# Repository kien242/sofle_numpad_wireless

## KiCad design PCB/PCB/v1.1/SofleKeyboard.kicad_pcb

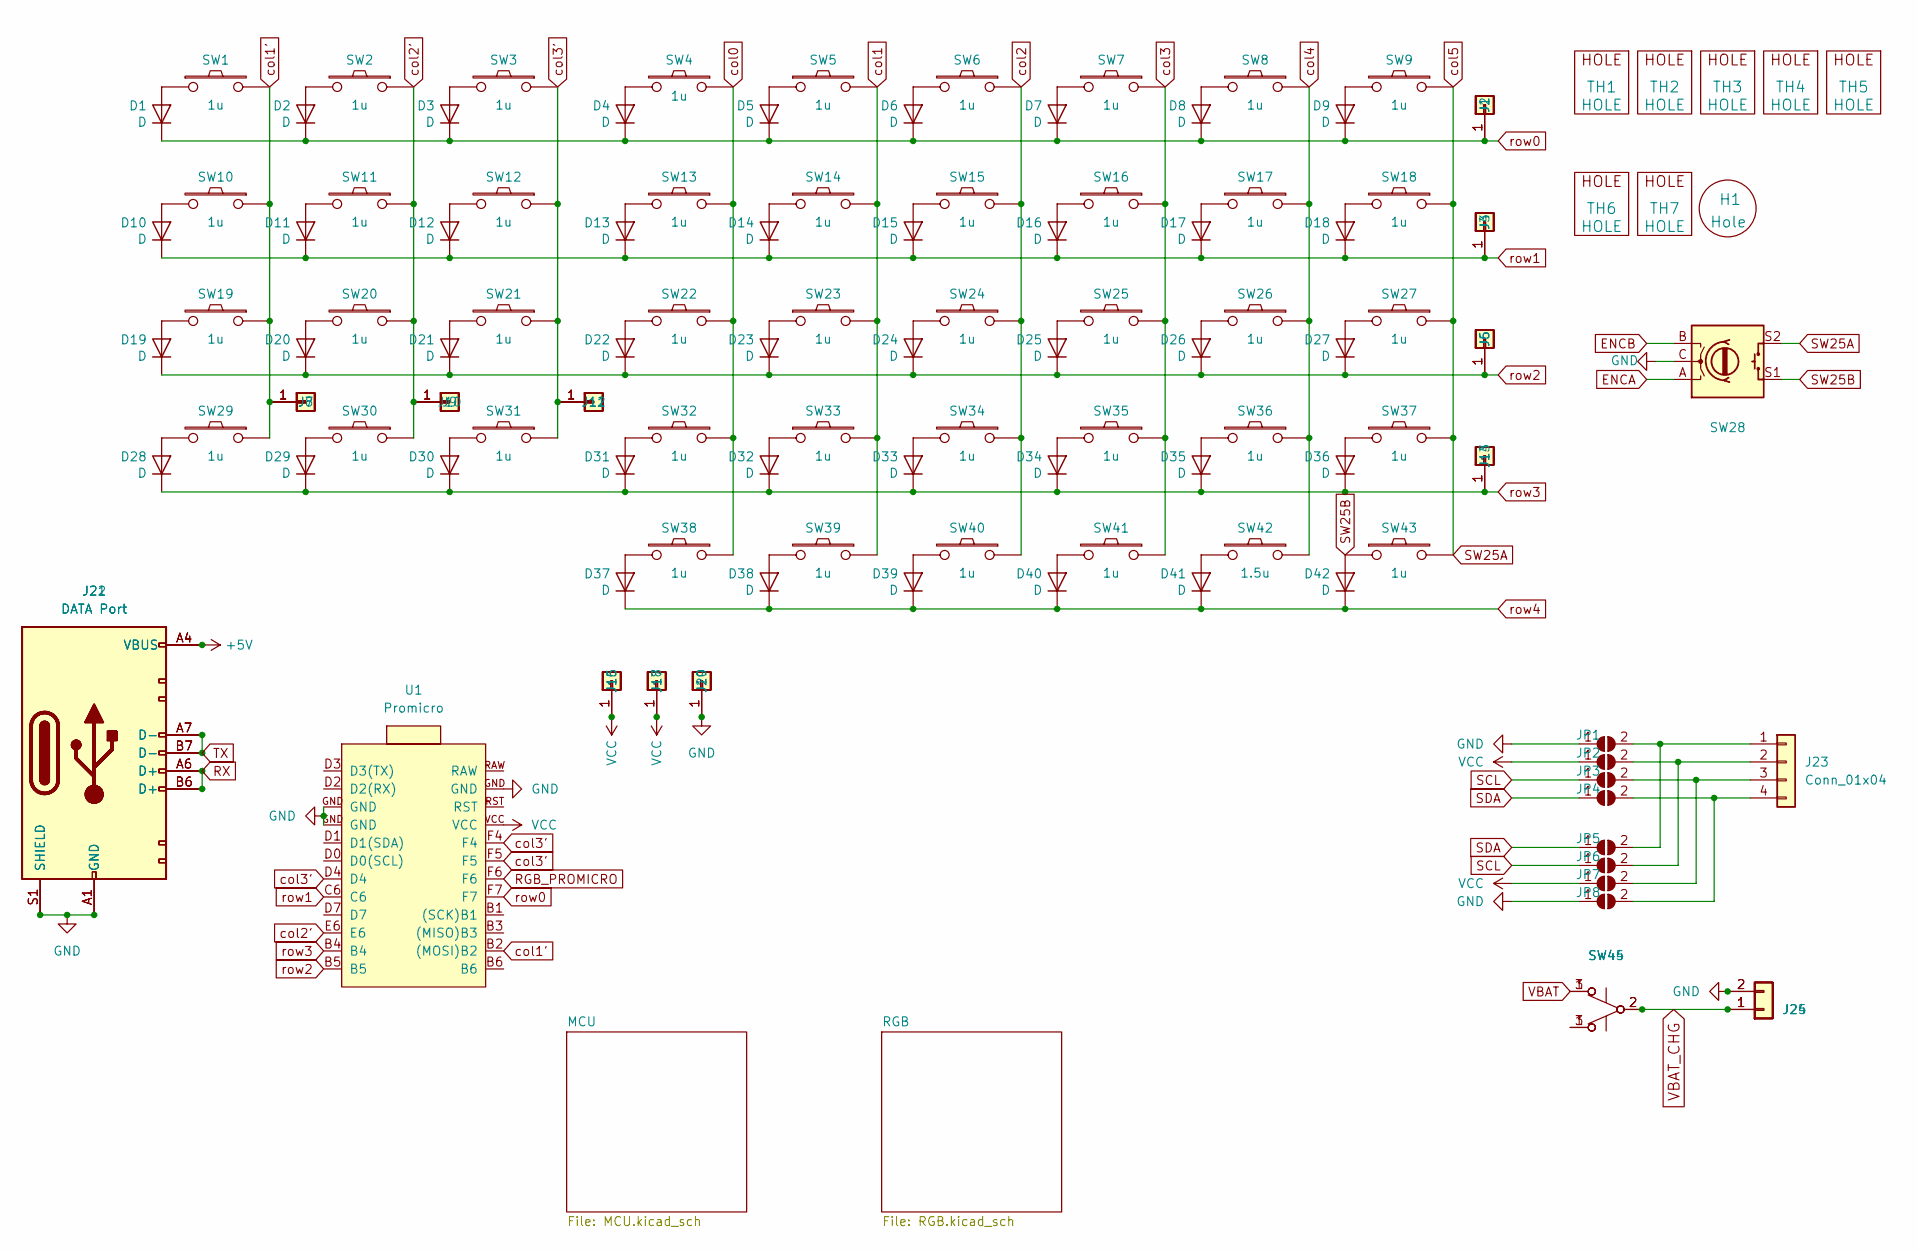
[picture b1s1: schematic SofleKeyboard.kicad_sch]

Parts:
D1, D2, D3, D4, D5, D6, D7, D8, D9, D10, D11, D12, D13, D14, D15, D16, D17, D18, D19, D20, D21, D22, D23, D24, D25, D26, D27, D28, D29, D30, D31, D32, D33, D34, D35, D36, D37, D38, D39, D40, D41, D42: D; Diode
H1: Hole; Cut_hole
J1, J2, J3, J4, J5, J6, J7, J8, J9, J10, J11, J12, J13, J14, J15, J16, J17, J18, J19, J20: Conn_01x01
J21, J22: DATA Port; USB-C-16pin-hight-v2
J23: Conn_01x04; 128x64OLED
J24, J25: JST_PH_S2B-PH-SM4-TB_1x02-1MP_P2.00mm_Horizontal
JP1, JP2, JP3, JP4: SolderJumper-2_P1.3mm_Open_RoundedPad1.0x1.5mm
JP5, JP6, JP7, JP8: SolderJumper-2_P1.3mm_Open_Pad1.0x1.5mm
SW1, SW2, SW3, SW4, SW5, SW6, SW7, SW8, SW9, SW10, SW13, SW14, SW15, SW16, SW17, SW18, SW19, SW20, SW21, SW22, SW23, SW24, SW25, SW26, SW27, SW29, SW30, SW31, SW32, SW33, SW34, SW35, SW36, SW37, SW38, SW39, SW40, SW41, SW43: 1u; SW-HS_flip-1u
SW11, SW12: 1u; SW-HS-Flip-1u
SW28: Econder
SW42: 1.5u; SW-HS_flip-1u
SW44, SW45: SW_SPDT_PCM12
TH1, TH2, TH3, TH4, TH5: HOLE; HOLE_M2_TH
TH6, TH7: HOLE; M2_HOLE_PCB
U1: Promicro; PRO-MICRO

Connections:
+5V: J21.A4 (VBUS), J21.A9 (VBUS), J21.B4 (VBUS), J21.B9 (VBUS), J22.A4 (VBUS), J22.A9 (VBUS), J22.B4 (VBUS), J22.B9 (VBUS); also elsewhere on the board
ENCA: SW28.A; also elsewhere on the board
ENCB: SW28.B; also elsewhere on the board
GND: J19.1, J20.1, J21.A1 (GND), J21.A12 (GND), J21.B1 (GND), J21.B12 (GND), J21.S1 (SHIELD), J22.A1 (GND), J22.A12 (GND), J22.B1 (GND), J22.B12 (GND), J22.S1 (SHIELD), J24.2, J25.2, JP1.1 (A), JP8.1 (A), SW28.C, U1.GND; also elsewhere on the board
unnamed: D1.2 (A), SW1.1
unnamed: D2.2 (A), SW2.2
unnamed: D3.2 (A), SW3.2
unnamed: D4.2 (A), SW4.2
unnamed: D5.2 (A), SW5.1
unnamed: D6.2 (A), SW6.2
unnamed: D7.2 (A), SW7.2
unnamed: D8.2 (A), SW8.2
unnamed: D9.2 (A), SW9.2
unnamed: D10.2 (A), SW10.2
unnamed: D11.2 (A), SW11.2
unnamed: D12.2 (A), SW12.2
unnamed: D13.2 (A), SW13.2
unnamed: D14.2 (A), SW14.1
unnamed: D15.2 (A), SW15.2
unnamed: D16.2 (A), SW16.2
unnamed: D17.2 (A), SW17.2
unnamed: D18.2 (A), SW18.2
unnamed: D19.2 (A), SW19.2
unnamed: D20.2 (A), SW20.2
unnamed: D21.2 (A), SW21.2
unnamed: D22.2 (A), SW22.2
unnamed: D23.2 (A), SW23.1
unnamed: D24.2 (A), SW24.2
unnamed: D25.2 (A), SW25.2
unnamed: D26.2 (A), SW26.2
unnamed: D27.2 (A), SW27.2
unnamed: D28.2 (A), SW29.2
unnamed: D29.2 (A), SW30.2
unnamed: D30.2 (A), SW31.2
unnamed: D31.2 (A), SW32.2
unnamed: D32.2 (A), SW33.1
unnamed: D33.2 (A), SW34.2
unnamed: D34.2 (A), SW35.2
unnamed: D35.2 (A), SW36.2
unnamed: D36.2 (A), SW37.2
unnamed: D37.2 (A), SW38.2
unnamed: D38.2 (A), SW39.2
unnamed: D39.2 (A), SW40.2
unnamed: D40.2 (A), SW41.2
unnamed: D41.2 (A), SW42.2
unnamed: J23.1, JP1.2 (B), JP5.2 (B)
unnamed: J23.2, JP2.2 (B), JP6.2 (B)
unnamed: J23.3, JP3.2 (B), JP7.2 (B)
unnamed: J23.4, JP4.2 (B), JP8.2 (B)
unnamed: SW44.3 (C), SW45.1 (A)
RGB_PROMICRO: U1.F6; also elsewhere on the board
RX: J21.A6 (D+), J21.B6 (D+), J22.A6 (D+), J22.B6 (D+); also elsewhere on the board
SCL: JP3.1 (A), JP6.1 (A); also elsewhere on the board
SDA: JP4.1 (A), JP5.1 (A); also elsewhere on the board
SW25A: SW9.1, SW18.1, SW27.1, SW28.S2, SW37.1, SW43.2; also elsewhere on the board
SW25B: D42.2 (A), SW28.S1, SW43.1
TX: J21.A7 (D-), J21.B7 (D-), J22.A7 (D-), J22.B7 (D-); also elsewhere on the board
VBAT: SW44.1 (A), SW45.3 (C); also elsewhere on the board
VBAT_CHG: J24.1, J25.1, SW44.2 (B), SW45.2 (B); also elsewhere on the board
VCC: J15.1, J16.1, J17.1, J18.1, JP2.1 (A), JP7.1 (A), U1.VCC; also elsewhere on the board
col0: SW4.1, SW13.1, SW22.1, SW32.1, SW38.1; also elsewhere on the board
col1: SW5.2, SW14.2, SW23.2, SW33.2, SW39.1; also elsewhere on the board
col1': J7.1, J8.1, SW1.2, SW10.1, SW19.1, SW29.1, U1.B2 ((MOSI)B2); also elsewhere on the board
col2: SW6.1, SW15.1, SW24.1, SW34.1, SW40.1; also elsewhere on the board
col2': J9.1, J10.1, SW2.1, SW11.1, SW20.1, SW30.1, U1.E6; also elsewhere on the board
col3: SW7.1, SW16.1, SW25.1, SW35.1, SW41.1; also elsewhere on the board
col3': J11.1, J12.1, SW3.1, SW12.1, SW21.1, SW31.1, U1.D4, U1.F4, U1.F5; also elsewhere on the board
col4: SW8.1, SW17.1, SW26.1, SW36.1, SW42.1; also elsewhere on the board
row0: D1.1 (K), D2.1 (K), D3.1 (K), D4.1 (K), D5.1 (K), D6.1 (K), D7.1 (K), D8.1 (K), D9.1 (K), J1.1, J2.1, U1.F7; also elsewhere on the board
row1: D10.1 (K), D11.1 (K), D12.1 (K), D13.1 (K), D14.1 (K), D15.1 (K), D16.1 (K), D17.1 (K), D18.1 (K), J3.1, J4.1, U1.C6; also elsewhere on the board
row2: D19.1 (K), D20.1 (K), D21.1 (K), D22.1 (K), D23.1 (K), D24.1 (K), D25.1 (K), D26.1 (K), D27.1 (K), J5.1, J6.1, U1.B5; also elsewhere on the board
row3: D28.1 (K), D29.1 (K), D30.1 (K), D31.1 (K), D32.1 (K), D33.1 (K), D34.1 (K), D35.1 (K), D36.1 (K), J13.1, J14.1, U1.B4; also elsewhere on the board
row4: D37.1 (K), D38.1 (K), D39.1 (K), D40.1 (K), D41.1 (K), D42.1 (K); also elsewhere on the board

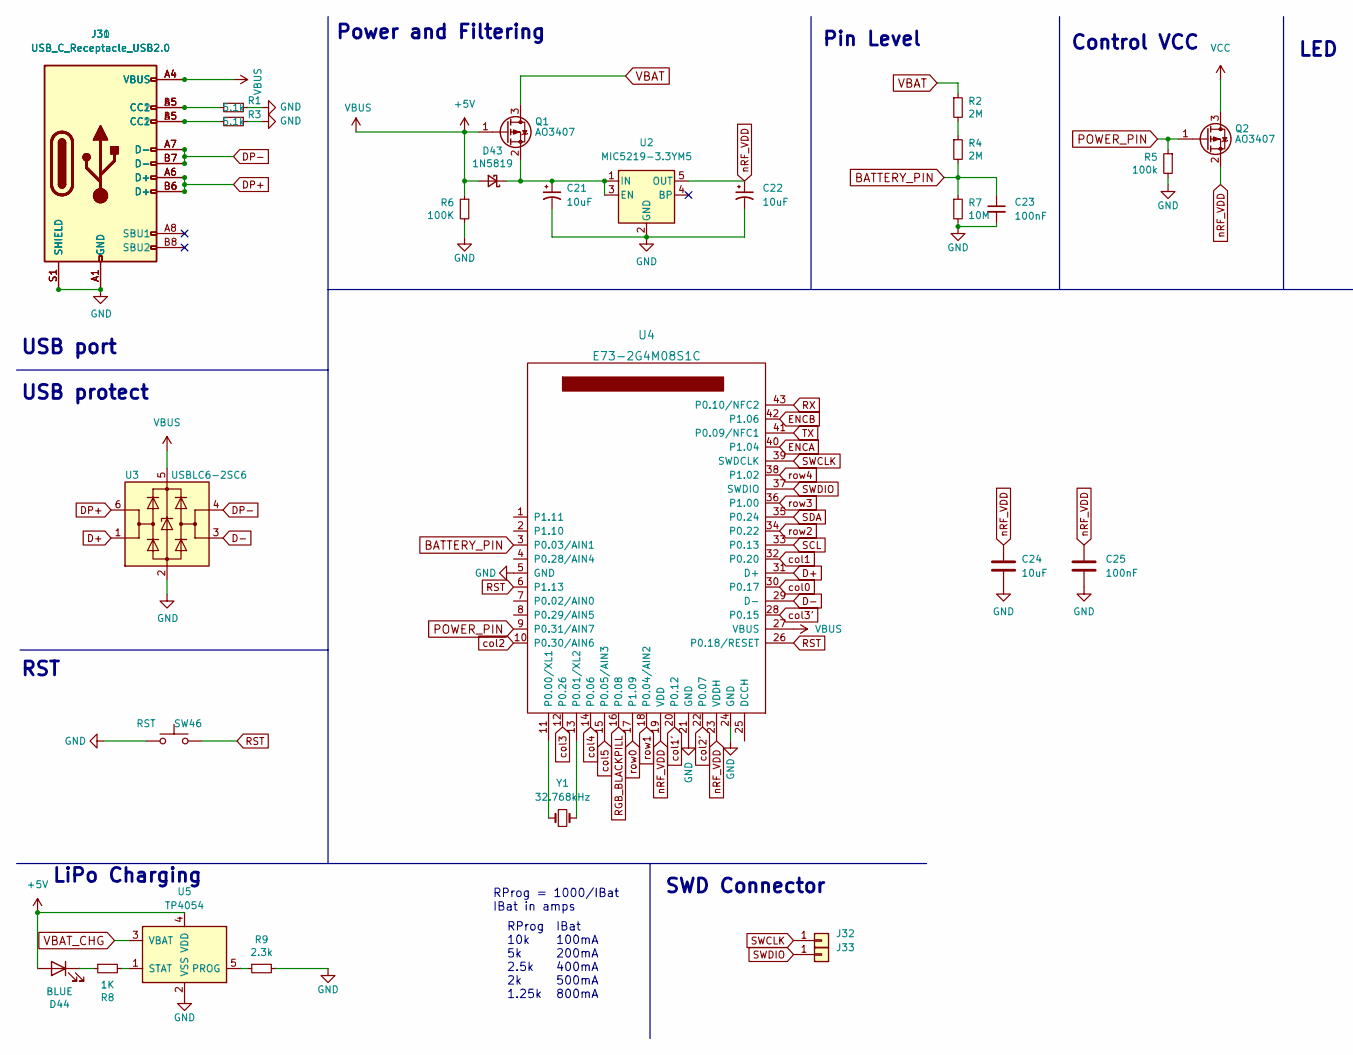
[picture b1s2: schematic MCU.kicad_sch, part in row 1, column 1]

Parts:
C21, C22: 10uF; CP_EIA-3216-12_Kemet-S
C23, C25: 100nF; C_0603_1608Metric
C24: 10uF; C_0603_1608Metric
D43: 1N5819; D_SOD-323_HandSoldering
D44: BLUE; LED_0603_1608Metric; LCSC Part Number C375446
J30, J31: USB_C_Receptacle_USB2.0; USB-C-16pin-hight-v2
J32: TestPoint_Pad_1.5x1.5mm
J33: TestPoint_Pad_D1.5mm
Q1, Q2: AO3407; SOT-23
R1, R3: 5.1k; R_0603_1608Metric
R2, R4: 2M; R_0603_1608Metric
R5: 100k; R_0603_1608Metric
R6: 100K; R_0603_1608Metric
R7: 10M; R_0603_1608Metric
R8: 1K; R_0603_1608Metric
R9: 2.3k; R_0603_1608Metric
SW46: RST; SW_SPST_TL3342
U2: MIC5219-3.3YM5; SOT-23-5
U3: USBLC6-2SC6; SOT-23-6
U4: E73-2G4M08S1C; E73-2G4M08S1C-kien242
U5: TP4054; SOT-23-5
Y1: 32.768kHz; Crystal_0603

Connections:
+5V: D43.2 (A), D44.2 (A), J30.A4 (VBUS), J30.A9 (VBUS), J30.B4 (VBUS), J30.B9 (VBUS), J31.A4 (VBUS), J31.A9 (VBUS), J31.B4 (VBUS), J31.B9 (VBUS), Q1.1 (G), R6.1, U3.5 (VBUS), U4.27 (VBUS), U5.4 (VDD); also elsewhere on the board
BATTERY_PIN: C23.1, R4.2, R7.1, U4.3 (P0.03/AIN1)
D+: U3.1 (I/O1), U4.31 (D+)
D-: U3.3 (I/O2), U4.29 (D-)
DP+: J30.A6 (D+), J30.B6 (D+), J31.A6 (D+), J31.B6 (D+), U3.6 (I/O1)
DP-: J30.A7 (D-), J30.B7 (D-), J31.A7 (D-), J31.B7 (D-), U3.4 (I/O2)
ENCA: U4.40 (P1.04); also elsewhere on the board
ENCB: U4.42 (P1.06); also elsewhere on the board
GND: C21.2, C22.2, C23.2, C24.2, C25.2, J30.A1 (GND), J30.A12 (GND), J30.B1 (GND), J30.B12 (GND), J30.S1 (SHIELD), J31.A1 (GND), J31.A12 (GND), J31.B1 (GND), J31.B12 (GND), J31.S1 (SHIELD), R1.2, R3.1, R5.2, R6.2, R7.2, R9.2, SW46.1, U2.2 (GND), U3.2 (GND), U4.5 (GND), U4.21 (GND), U4.24 (GND), U5.2 (VSS); also elsewhere on the board
unnamed: C21.1, D43.1 (K), Q1.2 (S), U2.1 (IN), U2.3 (EN)
unnamed: D44.1 (K), R8.1
unnamed: J30.A5 (CC1), J31.B5 (CC2), R3.2
unnamed: J30.B5 (CC2), J31.A5 (CC1), R1.1
unnamed: R2.2, R4.1
unnamed: U4.11 (P0.00/XL1), Y1.1
unnamed: U4.13 (P0.01/XL2), Y1.2
unnamed: R9.1, U5.5 (PROG)
unnamed: R8.2, U5.1 (STAT)
POWER_PIN: Q2.1 (G), R5.1, U4.9 (P0.31/AIN7)
RGB_BLACKPILL: U4.16 (P0.08); also elsewhere on the board
RST: SW46.2, U4.6 (P1.13), U4.26 (P0.18/RESET); also elsewhere on the board
RX: U4.43 (P0.10/NFC2); also elsewhere on the board
SCL: U4.33 (P0.13); also elsewhere on the board
SDA: U4.35 (P0.24); also elsewhere on the board
SW25A: U4.15 (P0.05/AIN3); also elsewhere on the board
SWCLK: J32.1, U4.39 (SWDCLK)
SWDIO: J33.1, U4.37 (SWDIO)
TX: U4.41 (P0.09/NFC1); also elsewhere on the board
VBAT: Q1.3 (D), R2.1; also elsewhere on the board
VBAT_CHG: U5.3 (VBAT); also elsewhere on the board
VCC: Q2.3 (D); also elsewhere on the board
col0: U4.30 (P0.17); also elsewhere on the board
col1: U4.32 (P0.20); also elsewhere on the board
col1': U4.20 (P0.12); also elsewhere on the board
col2: U4.10 (P0.30/AIN6); also elsewhere on the board
col2': U4.22 (P0.07); also elsewhere on the board
col3: U4.12 (P0.26); also elsewhere on the board
col3': U4.28 (P0.15); also elsewhere on the board
col4: U4.14 (P0.06); also elsewhere on the board
nRF_VDD: C22.1, C24.1, C25.1, Q2.2 (S), U2.5 (OUT), U4.19 (VDD), U4.23 (VDDH)
row0: U4.17 (P1.09); also elsewhere on the board
row1: U4.18 (P0.04/AIN2); also elsewhere on the board
row2: U4.34 (P0.22); also elsewhere on the board
row3: U4.36 (P1.00); also elsewhere on the board
row4: U4.38 (P1.02); also elsewhere on the board

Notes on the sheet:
SWD Connector
Pin Level
IBat 100mA 200mA 400mA 500mA 800mA
USB port
RProg 10k 5k 2.5k 2k 1.25k
USB protect
LED
Power and Filtering
Control VCC
LiPo Charging
RProg = 1000/IBat IBat in amps
RST

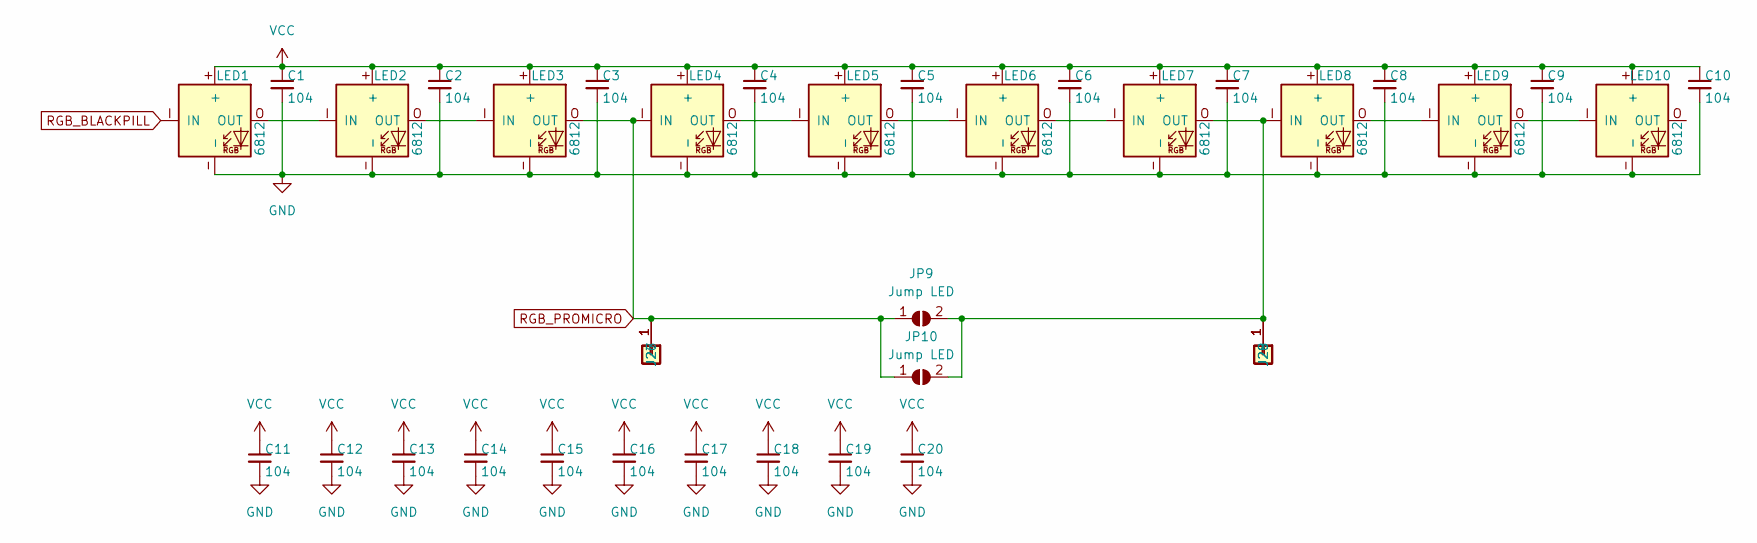
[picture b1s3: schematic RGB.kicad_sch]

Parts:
C1, C2, C3, C4, C5, C6, C7, C8, C9, C10, C11, C12, C13, C14, C15, C16, C17, C18, C19, C20: 104; C_0603_1608Metric
J26, J27, J28, J29: Conn_01x01
JP9: Jump LED; SolderJumper-2_P1.3mm_Open_RoundedPad1.0x1.5mm
JP10: Jump LED; SolderJumper-2_P1.3mm_Open_Pad1.0x1.5mm
LED1, LED2, LED3, LED4, LED5, LED6, LED7, LED8, LED9, LED10: 6812; SK6812MINI-FLIP

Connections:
GND: C1.2, C2.2, C3.2, C4.2, C5.2, C6.2, C7.2, C8.2, C9.2, C10.2, C11.2, C12.2, C13.2, C14.2, C15.2, C16.2, C17.2, C18.2, C19.2, C20.2, LED1.-, LED2.-, LED3.-, LED4.-, LED5.-, LED6.-, LED7.-, LED8.-, LED9.-, LED10.-; also elsewhere on the board
unnamed: J28.1, J29.1, JP9.2 (B), JP10.2 (B), LED7.O (OUT), LED8.I (IN)
unnamed: LED1.O (OUT), LED2.I (IN)
unnamed: LED2.O (OUT), LED3.I (IN)
unnamed: LED4.O (OUT), LED5.I (IN)
unnamed: LED5.O (OUT), LED6.I (IN)
unnamed: LED6.O (OUT), LED7.I (IN)
unnamed: LED8.O (OUT), LED9.I (IN)
unnamed: LED9.O (OUT), LED10.I (IN)
RGB_BLACKPILL: LED1.I (IN); also elsewhere on the board
RGB_PROMICRO: J26.1, J27.1, JP9.1 (A), JP10.1 (A), LED3.O (OUT), LED4.I (IN); also elsewhere on the board
VCC: C1.1, C2.1, C3.1, C4.1, C5.1, C6.1, C7.1, C8.1, C9.1, C10.1, C11.1, C12.1, C13.1, C14.1, C15.1, C16.1, C17.1, C18.1, C19.1, C20.1, LED1.+, LED2.+, LED3.+, LED4.+, LED5.+, LED6.+, LED7.+, LED8.+, LED9.+, LED10.+; also elsewhere on the board

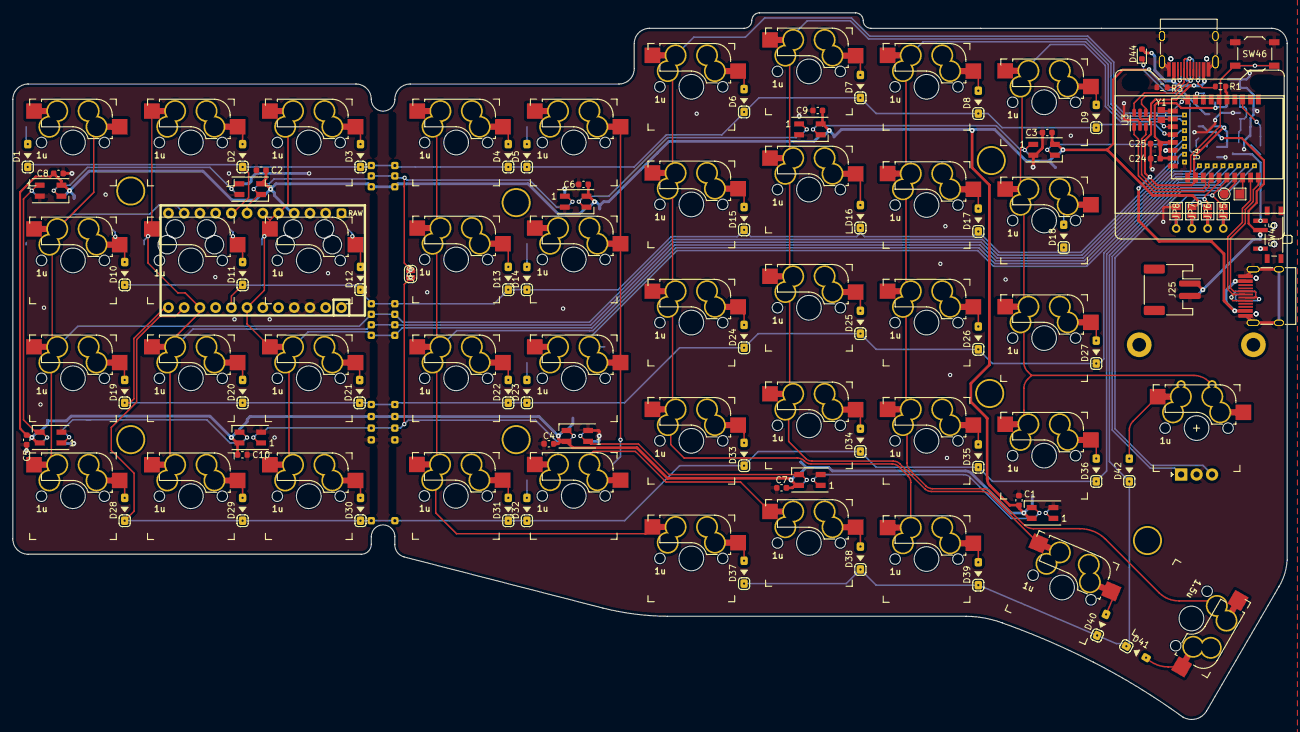
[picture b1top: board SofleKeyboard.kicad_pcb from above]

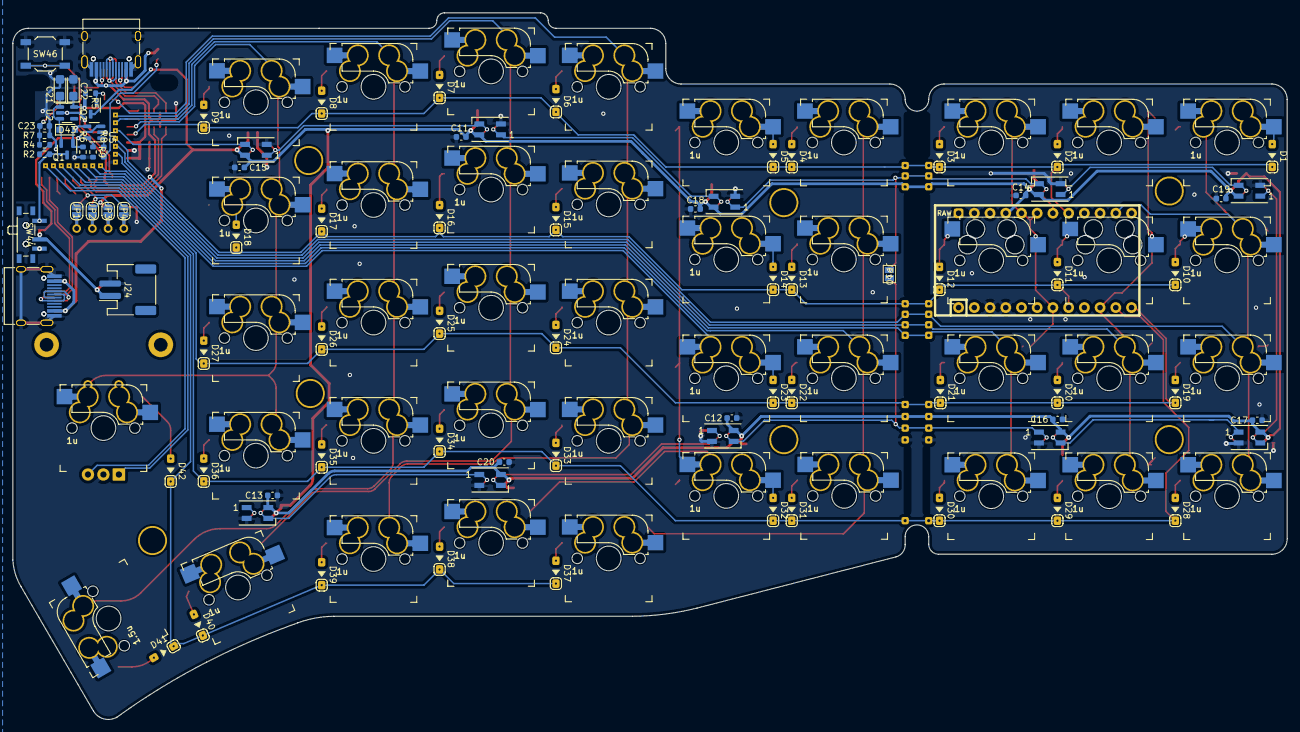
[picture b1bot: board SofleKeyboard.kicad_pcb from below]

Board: 2 copper layers, 205.9 x 114.2 mm, 203 parts (78 on the bottom side), 101 nets.

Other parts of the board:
H1#2, H1#3, H1#4, H1#5, H1#6, H1#7, H1#8: Hole; Cut_hole
SW46#2: RST; SW_SPST_TL3342
TH4#2, TH4#3: HOLE; HOLE_M2_TH

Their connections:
GND: SW46#2.1; also elsewhere on the board
RST: SW46#2.2; also elsewhere on the board

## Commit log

2022-09-06 update PCB file
2022-09-06 update PCB
2023-01-18 cap nhat
